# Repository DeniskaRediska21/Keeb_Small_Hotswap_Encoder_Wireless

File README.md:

# Split Ergo Ortholinear Hotswap Keyboard 

This project attempts to create easelly reproducible split ortholinear  hotswap mechanical
keyboard. 

Gimmics: 
+ This design doesn't require any diodes
+ Uses PiPico as MC, runs on CircuitPython
+ Key layouts are changed by dragging a file onto PiPicos storrage
+ Halves are connected through TypeC
+ PCB fits into 100x100mm square, so it is very cheap to order from Chineese manifacturers

# Gallery

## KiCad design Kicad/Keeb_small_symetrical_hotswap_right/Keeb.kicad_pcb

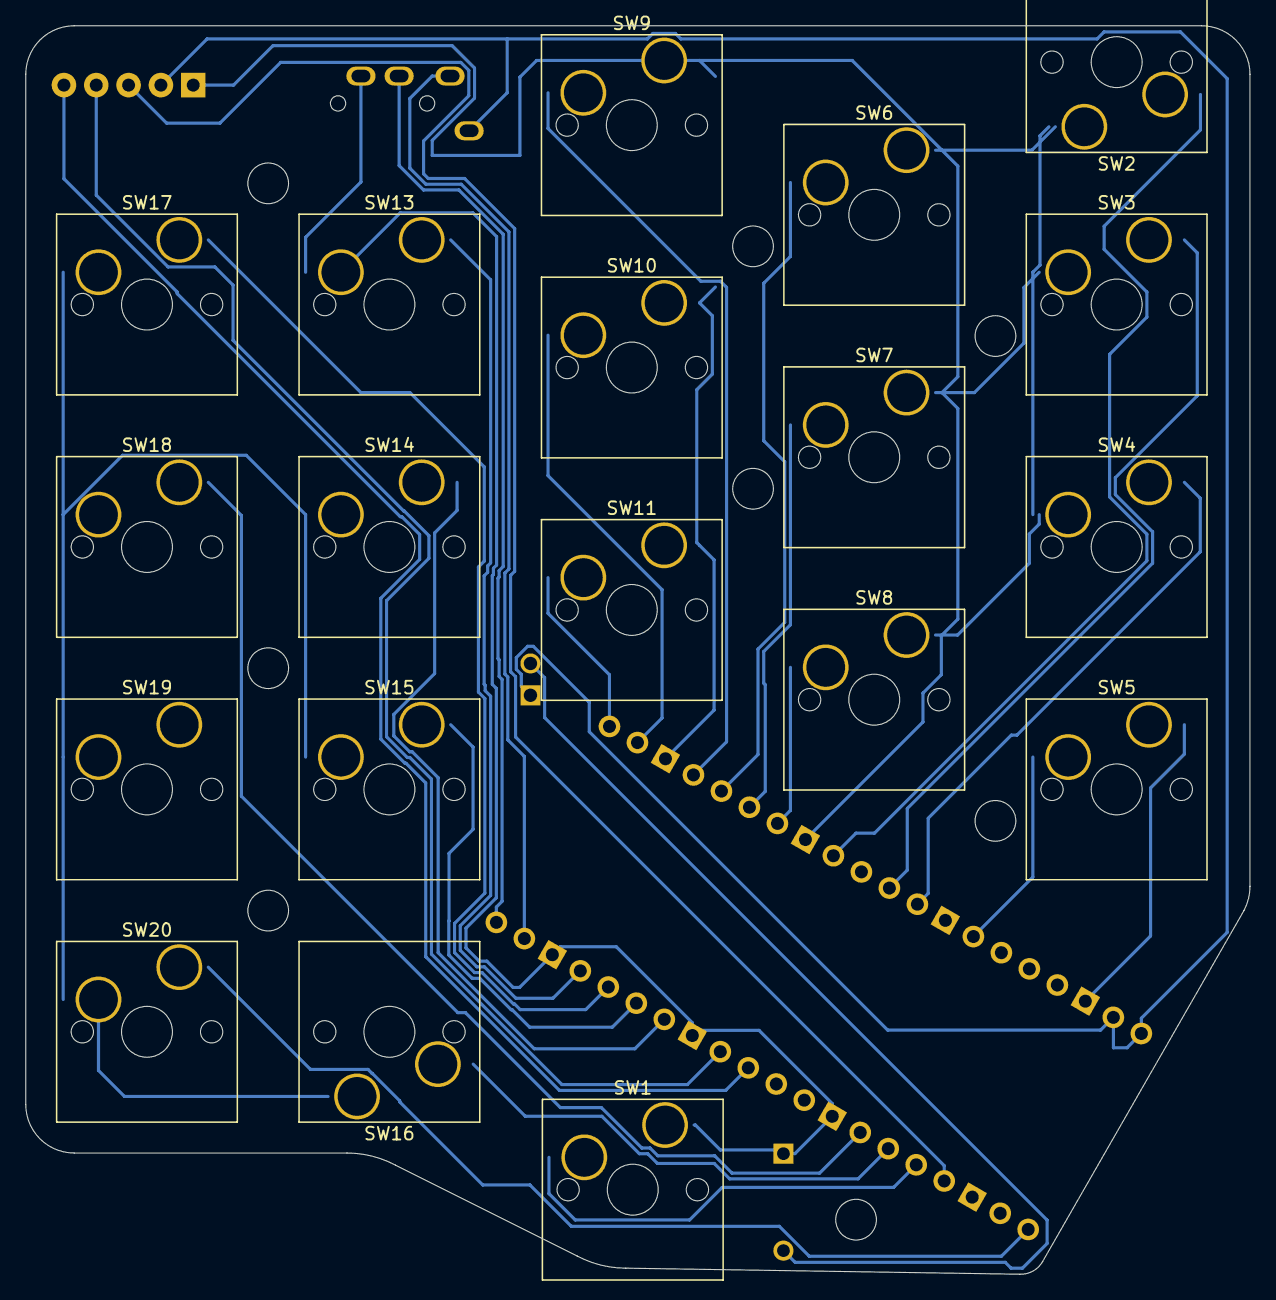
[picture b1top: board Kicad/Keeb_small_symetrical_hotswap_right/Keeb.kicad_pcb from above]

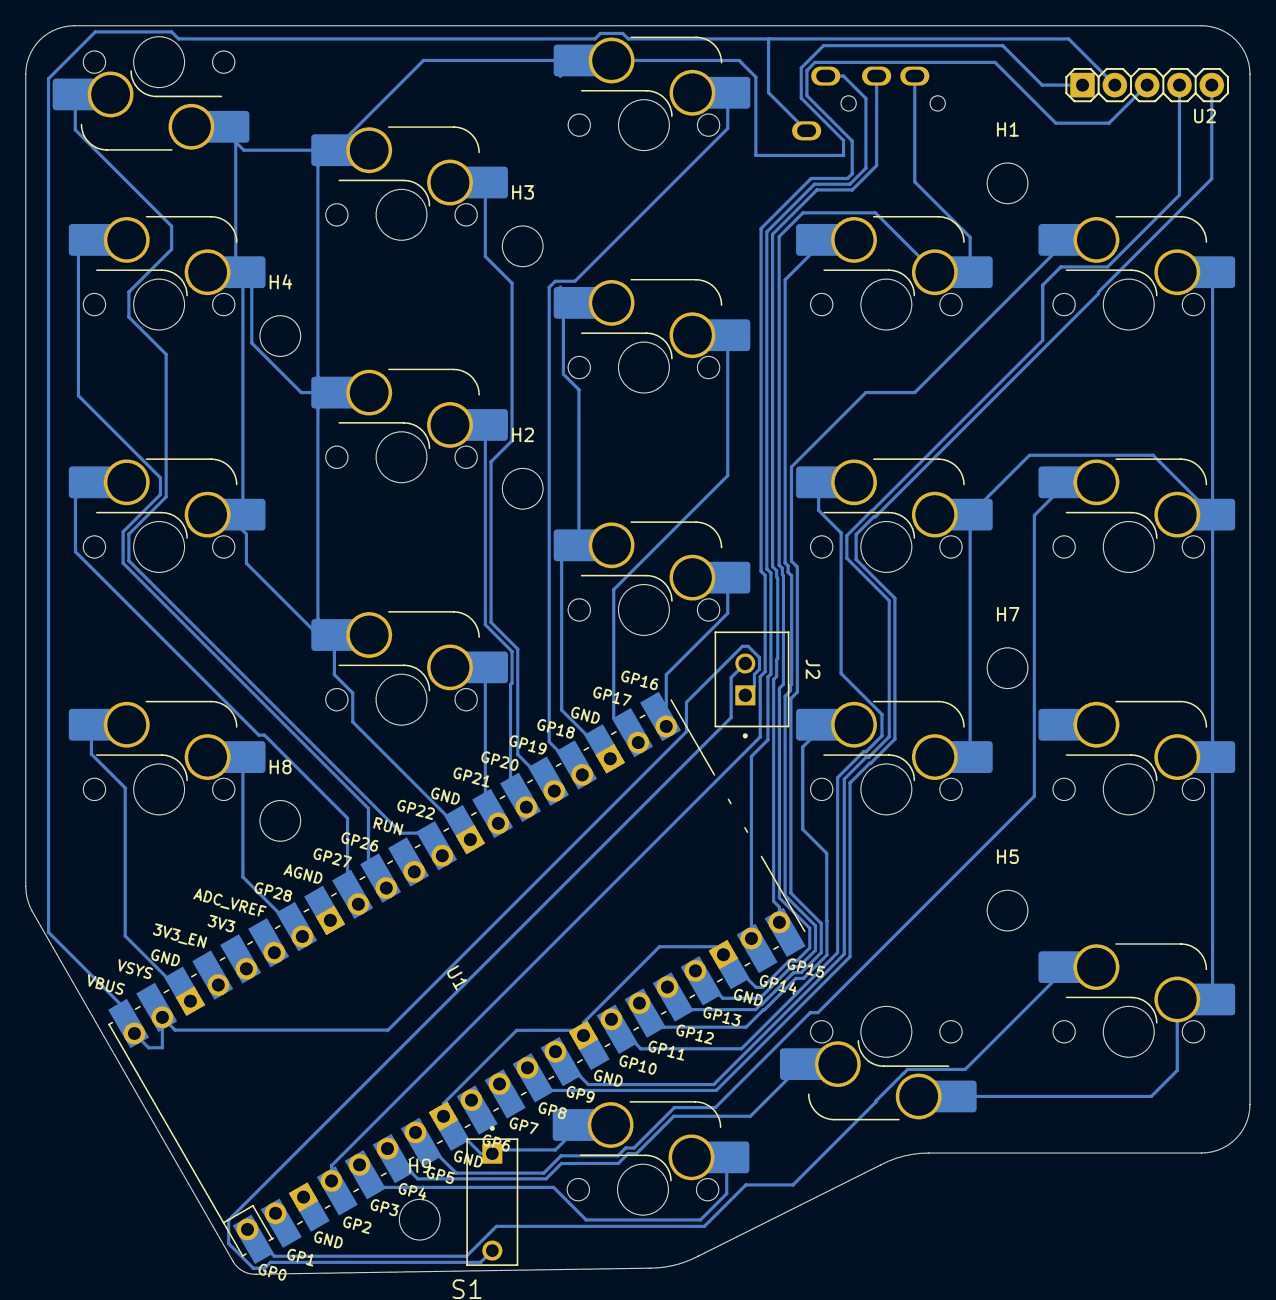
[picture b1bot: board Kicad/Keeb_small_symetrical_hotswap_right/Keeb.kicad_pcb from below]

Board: 2 copper layers, 96.2 x 98.1 mm, 32 parts (12 on the bottom side), 27 nets.

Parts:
H1, H2, H3, H4, H5, H7, H8, H9: MountingHole; MountingHole_3.2mm_M3
J2: B2B-XH-A_LF__SN_; JST_B2B-XH-A_LF__SN_
J3: MJ-4PP-9_MJ-4PP-9; MJ-4PP-9_no_silk
S1: DS01-254-L-01BE; SW_DS01-254-L-01BE
SW1, SW2, SW3, SW4, SW5, SW6, SW7, SW8, SW9, SW10, SW11, SW13, SW14, SW15, SW16, SW17, SW18, SW19, SW20: CherryMX; Hotswap_MX_Plated_1.00u
U1: Pico; RPi_Pico_SMD_TH_NO_BACK_HOLES
U2: KY-040; KY-040-PORT

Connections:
0: SW20.2, U1.1 (GPIO0)
1: SW19.2, U1.2 (GPIO1)
2: U1.4 (GPIO2), U2.SW
3: SW1.1, U1.5 (GPIO3)
3v3: J2.1, J3.1 (A), U1.39 (VSYS), U1.40 (VBUS), U2.VCC
4: SW16.1, U1.6 (GPIO4)
5: SW18.2, U1.7 (GPIO5)
8: U1.11 (GPIO8), U2.CLK
9: U1.12 (GPIO9), U2.DT
10: SW14.2, U1.14 (GPIO10)
11: SW15.2, U1.15 (GPIO11)
12: SW17.2, U1.16 (GPIO12)
13: SW13.2, U1.17 (GPIO13)
14: J3.4 (D), U1.19 (GPIO14)
15: J3.3 (C), U1.20 (GPIO15)
16: SW11.1, U1.21 (GPIO16)
17: SW10.1, U1.22 (GPIO17)
18: SW9.1, U1.24 (GPIO18)
19: SW6.1, U1.25 (GPIO19)
20: SW7.1, U1.26 (GPIO20)
21: SW8.1, U1.27 (GPIO21)
22: SW2.1, U1.29 (GPIO22)
26: SW3.2, U1.31 (GPIO26_ADC0)
27: SW4.2, U1.32 (GPIO27_ADC1)
28: SW5.1, U1.34 (GPIO28_ADC2)
GND: J3.2 (B), S1.1A, SW1.2, SW2.2, SW3.1, SW4.1, SW5.2, SW6.2, SW7.2, SW8.2, SW9.2, SW10.2, SW11.2, SW13.1, SW14.1, SW15.1, SW16.2, SW17.1, SW18.1, SW19.1, SW20.1, U1.3 (GND), U1.8 (GND), U1.13 (GND), U1.18 (GND), U1.23 (GND), U1.28 (GND), U1.33 (AGND), U1.38 (GND), U2.GND
unnamed: J2.2, S1.1B

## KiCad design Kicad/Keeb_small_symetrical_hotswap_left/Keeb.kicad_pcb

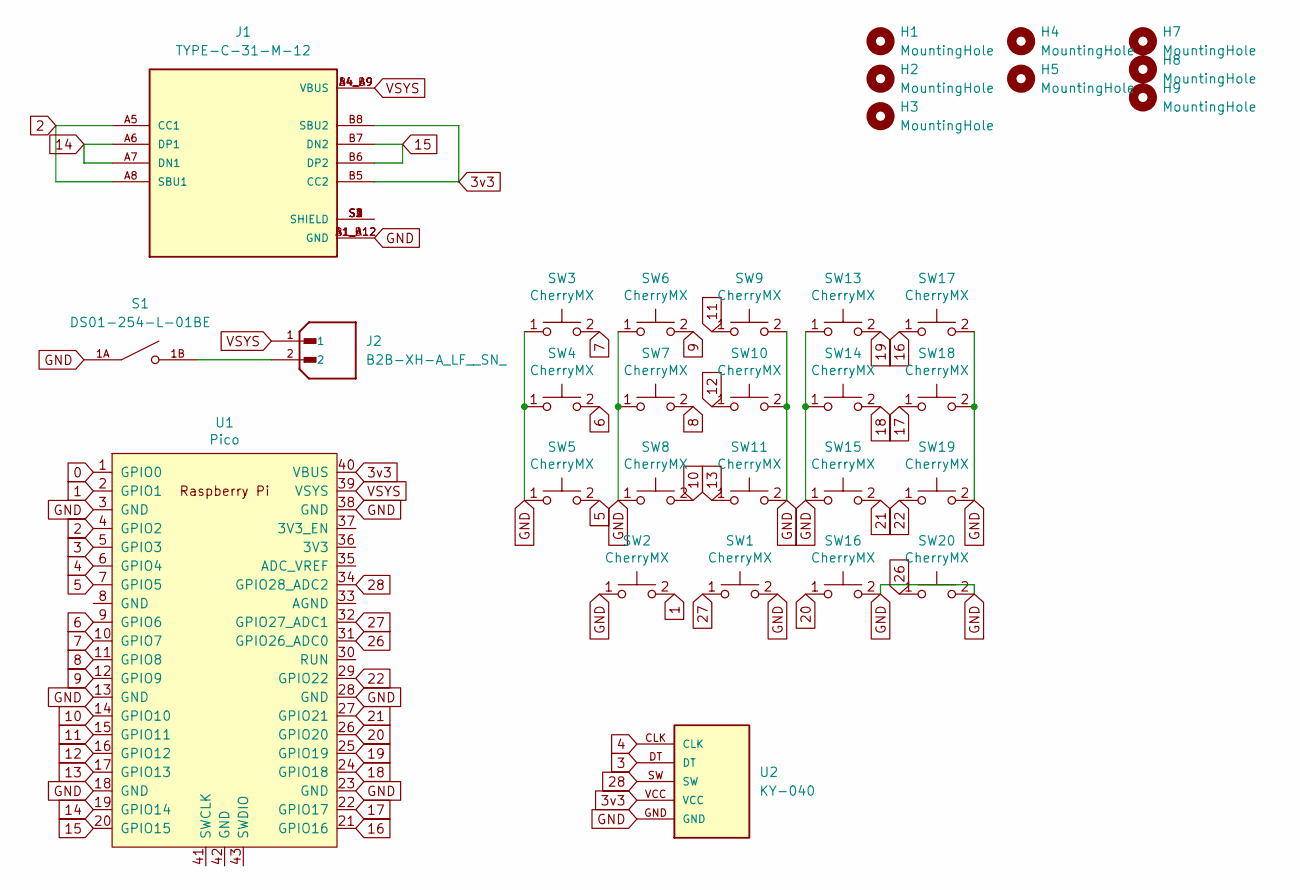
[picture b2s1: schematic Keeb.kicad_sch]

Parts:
H1, H2, H3, H4, H5, H7, H8, H9: MountingHole; MountingHole_3.2mm_M3
J1: TYPE-C-31-M-12; HRO_TYPE-C-31-M-12; PARTREV 2020.12.08
J2: B2B-XH-A_LF__SN_; JST_B2B-XH-A_LF__SN_; PARTREV N/A
S1: DS01-254-L-01BE; SW_DS01-254-L-01BE; PARTREV 1.0
SW1, SW2, SW3, SW4, SW5, SW6, SW7, SW8, SW9, SW10, SW11, SW13, SW14, SW15, SW16, SW17, SW18, SW19, SW20: CherryMX; Hotswap_MX_Plated_1.00u_Smaller_hole
U1: Pico; RPi_Pico_SMD_TH_NO_BACK_HOLES
U2: KY-040; KY-040-PORT

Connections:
0: U1.1 (GPIO0)
1: SW2.2, U1.2 (GPIO1)
2: J1.A5 (CC1), J1.A8 (SBU1), U1.4 (GPIO2)
3: U1.5 (GPIO3), U2.DT
3v3: J1.B5 (CC2), J1.B8 (SBU2), U1.40 (VBUS), U2.VCC
4: U1.6 (GPIO4), U2.CLK
5: SW5.2, U1.7 (GPIO5)
6: SW4.2, U1.9 (GPIO6)
7: SW3.2, U1.10 (GPIO7)
8: SW7.2, U1.11 (GPIO8)
9: SW6.2, U1.12 (GPIO9)
10: SW8.2, U1.14 (GPIO10)
11: SW9.1, U1.15 (GPIO11)
12: SW10.1, U1.16 (GPIO12)
13: SW11.1, U1.17 (GPIO13)
14: J1.A6 (DP1), J1.A7 (DN1), U1.19 (GPIO14)
15: J1.B6 (DP2), J1.B7 (DN2), U1.20 (GPIO15)
16: SW17.1, U1.21 (GPIO16)
17: SW18.1, U1.22 (GPIO17)
18: SW14.2, U1.24 (GPIO18)
19: SW13.2, U1.25 (GPIO19)
20: SW16.1, U1.26 (GPIO20)
21: SW15.2, U1.27 (GPIO21)
22: SW19.1, U1.29 (GPIO22)
26: SW20.1, U1.31 (GPIO26_ADC0)
27: SW1.1, U1.32 (GPIO27_ADC1)
28: U1.34 (GPIO28_ADC2), U2.SW
GND: J1.A1_B12 (GND), J1.B1_A12 (GND), S1.1A, SW1.2, SW2.1, SW3.1, SW4.1, SW5.1, SW6.1, SW7.1, SW8.1, SW9.2, SW10.2, SW11.2, SW13.1, SW14.1, SW15.1, SW16.2, SW17.2, SW18.2, SW19.2, SW20.2, U1.3 (GND), U1.13 (GND), U1.18 (GND), U1.23 (GND), U1.28 (GND), U1.38 (GND), U2.GND
unnamed: J1.S1 (SHIELD), J1.S2 (SHIELD), J1.S3 (SHIELD), J1.S4 (SHIELD)
unnamed: J2.2, S1.1B
VSYS: J1.A4_B9 (VBUS), J1.B4_A9 (VBUS), J2.1, U1.39 (VSYS)

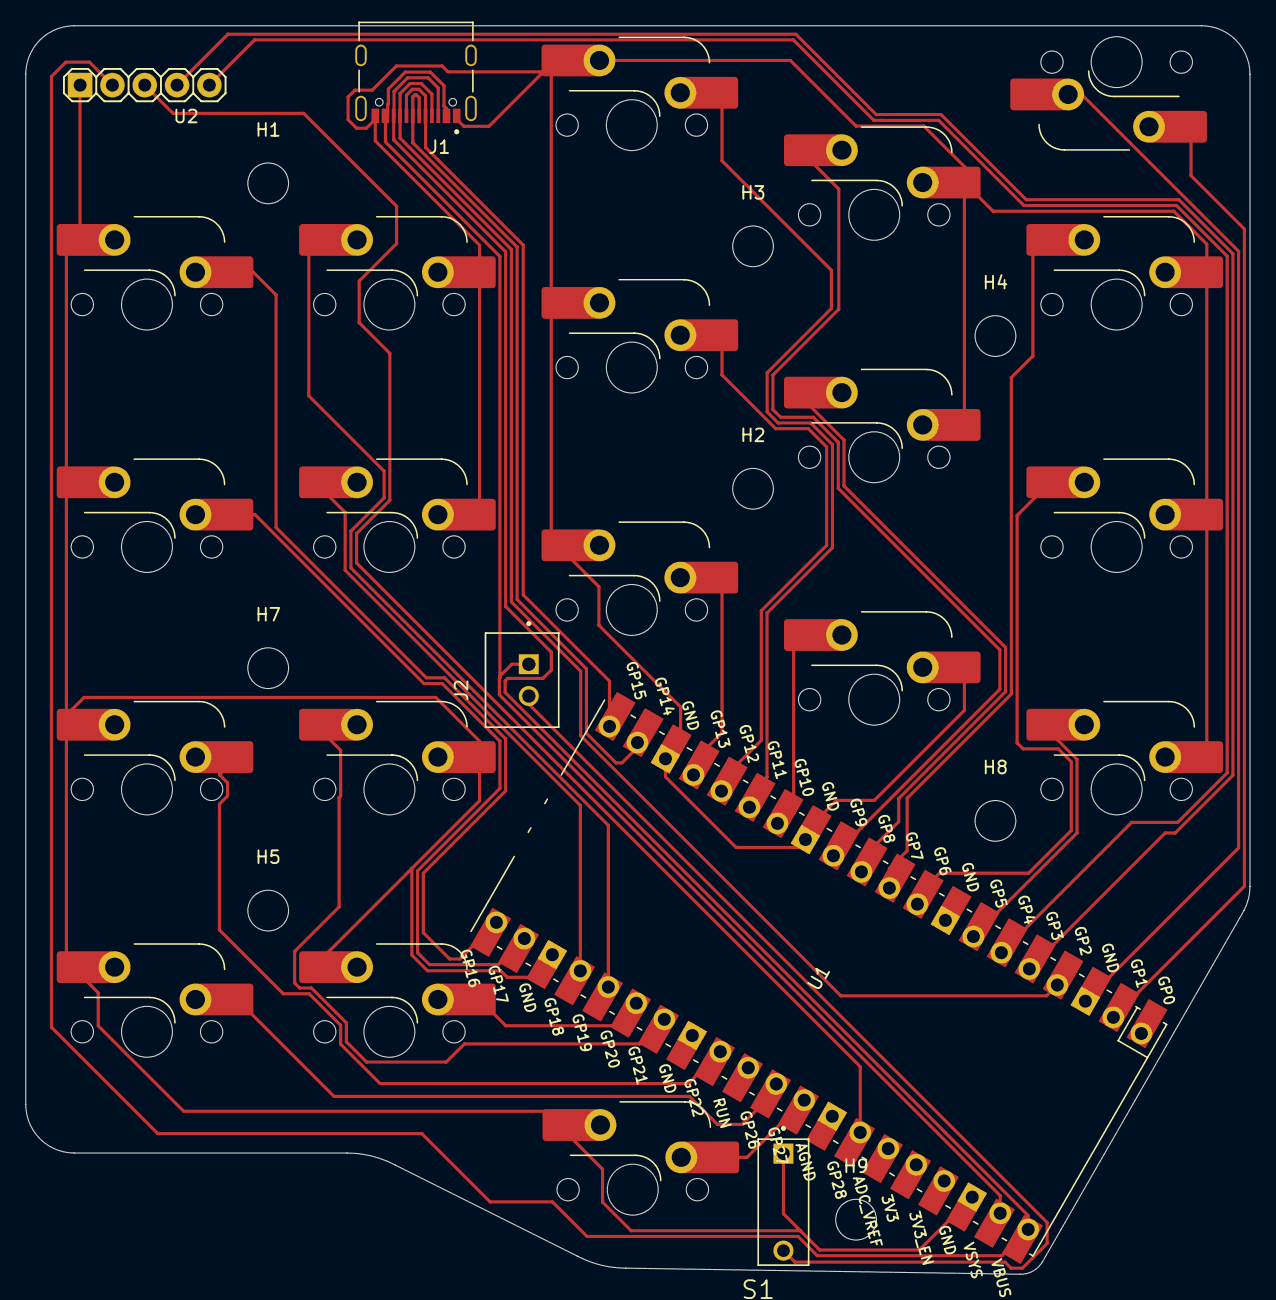
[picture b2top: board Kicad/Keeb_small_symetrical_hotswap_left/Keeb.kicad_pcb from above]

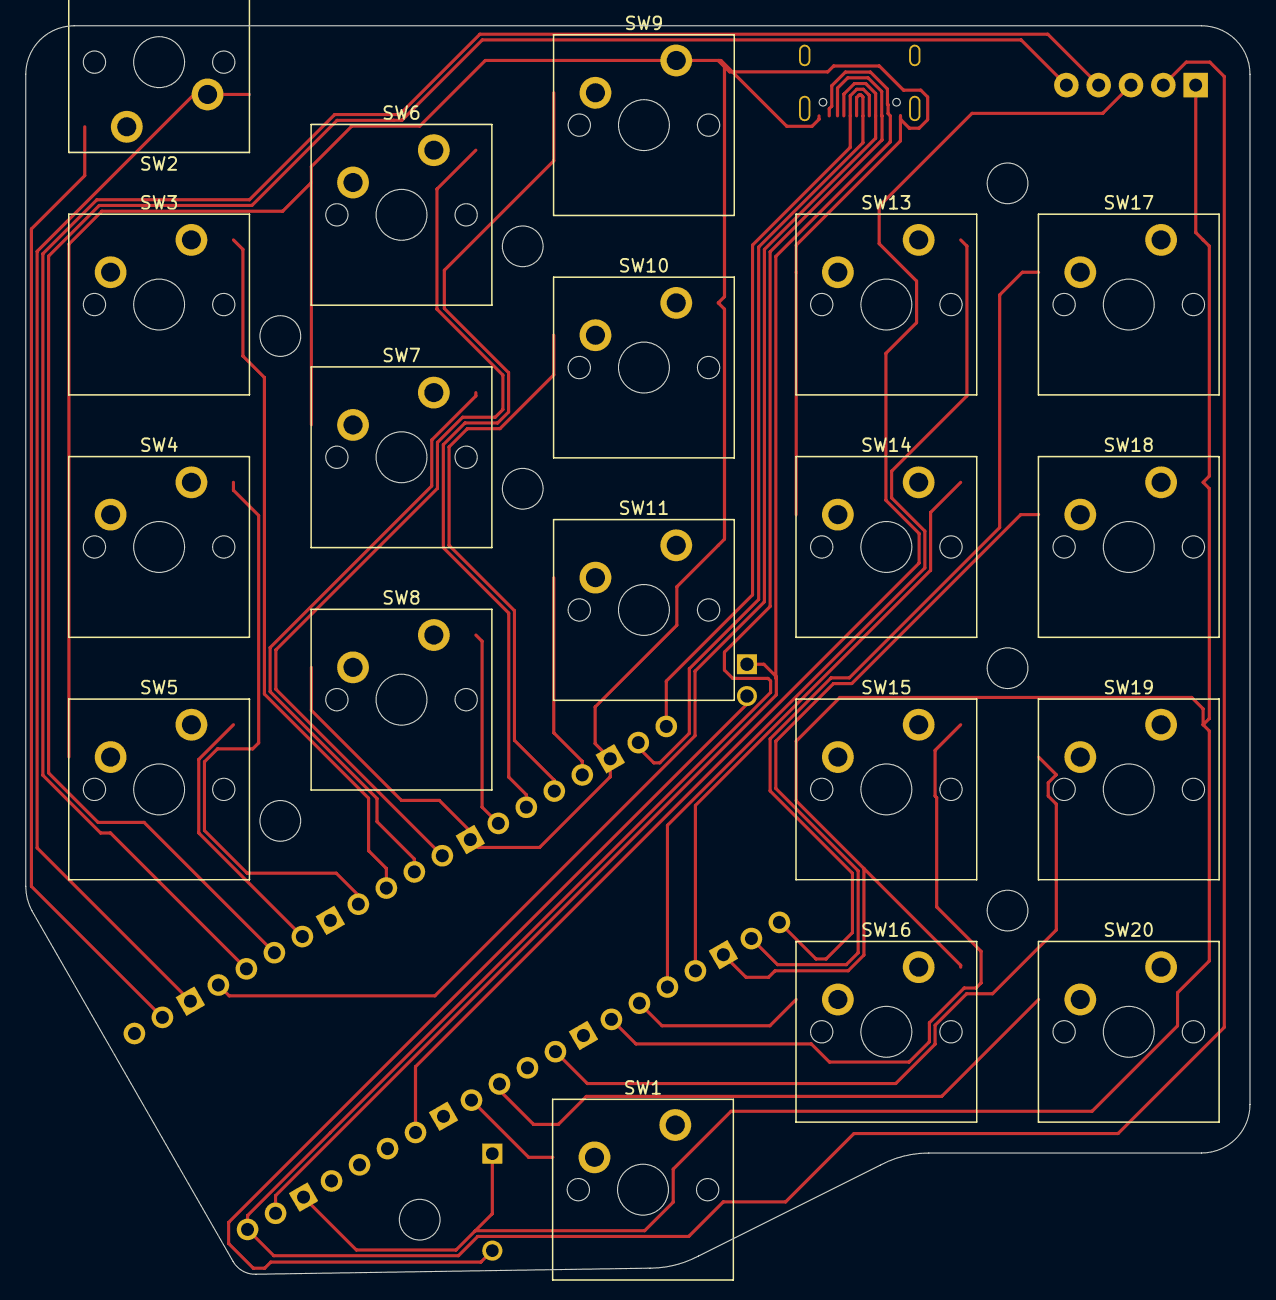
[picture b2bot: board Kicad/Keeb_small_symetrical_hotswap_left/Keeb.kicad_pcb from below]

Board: 2 copper layers, 96.2 x 98.1 mm, 32 parts (19 on the bottom side), 30 nets.

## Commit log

2023-12-06 init
2023-12-06 added encoder
2023-12-07 moved some traces
2023-12-08 Managed to add a button, optimised tracks, switched some connections around
2023-12-08 Worked a bit on the edge-cuts
2023-12-08 Addedthe photo of board
2023-12-08 Updated a PiPico footprint
2023-12-08 added more fillets
2023-12-08 added a connectior for the battery
2023-12-08 added a on/off
2023-12-08 new photo
2023-12-10 Switched footprint to copper plater one to give an opiton of soldering switches directly
2023-12-10 routing
2023-12-10 Almost dome with right half
2023-12-10 Fixedright board
2023-12-10 added photo
2023-12-10 Added gerbers
2024-01-22 Added software
2024-01-22 N->M
2024-01-22 Implemented encoders on the split halves
